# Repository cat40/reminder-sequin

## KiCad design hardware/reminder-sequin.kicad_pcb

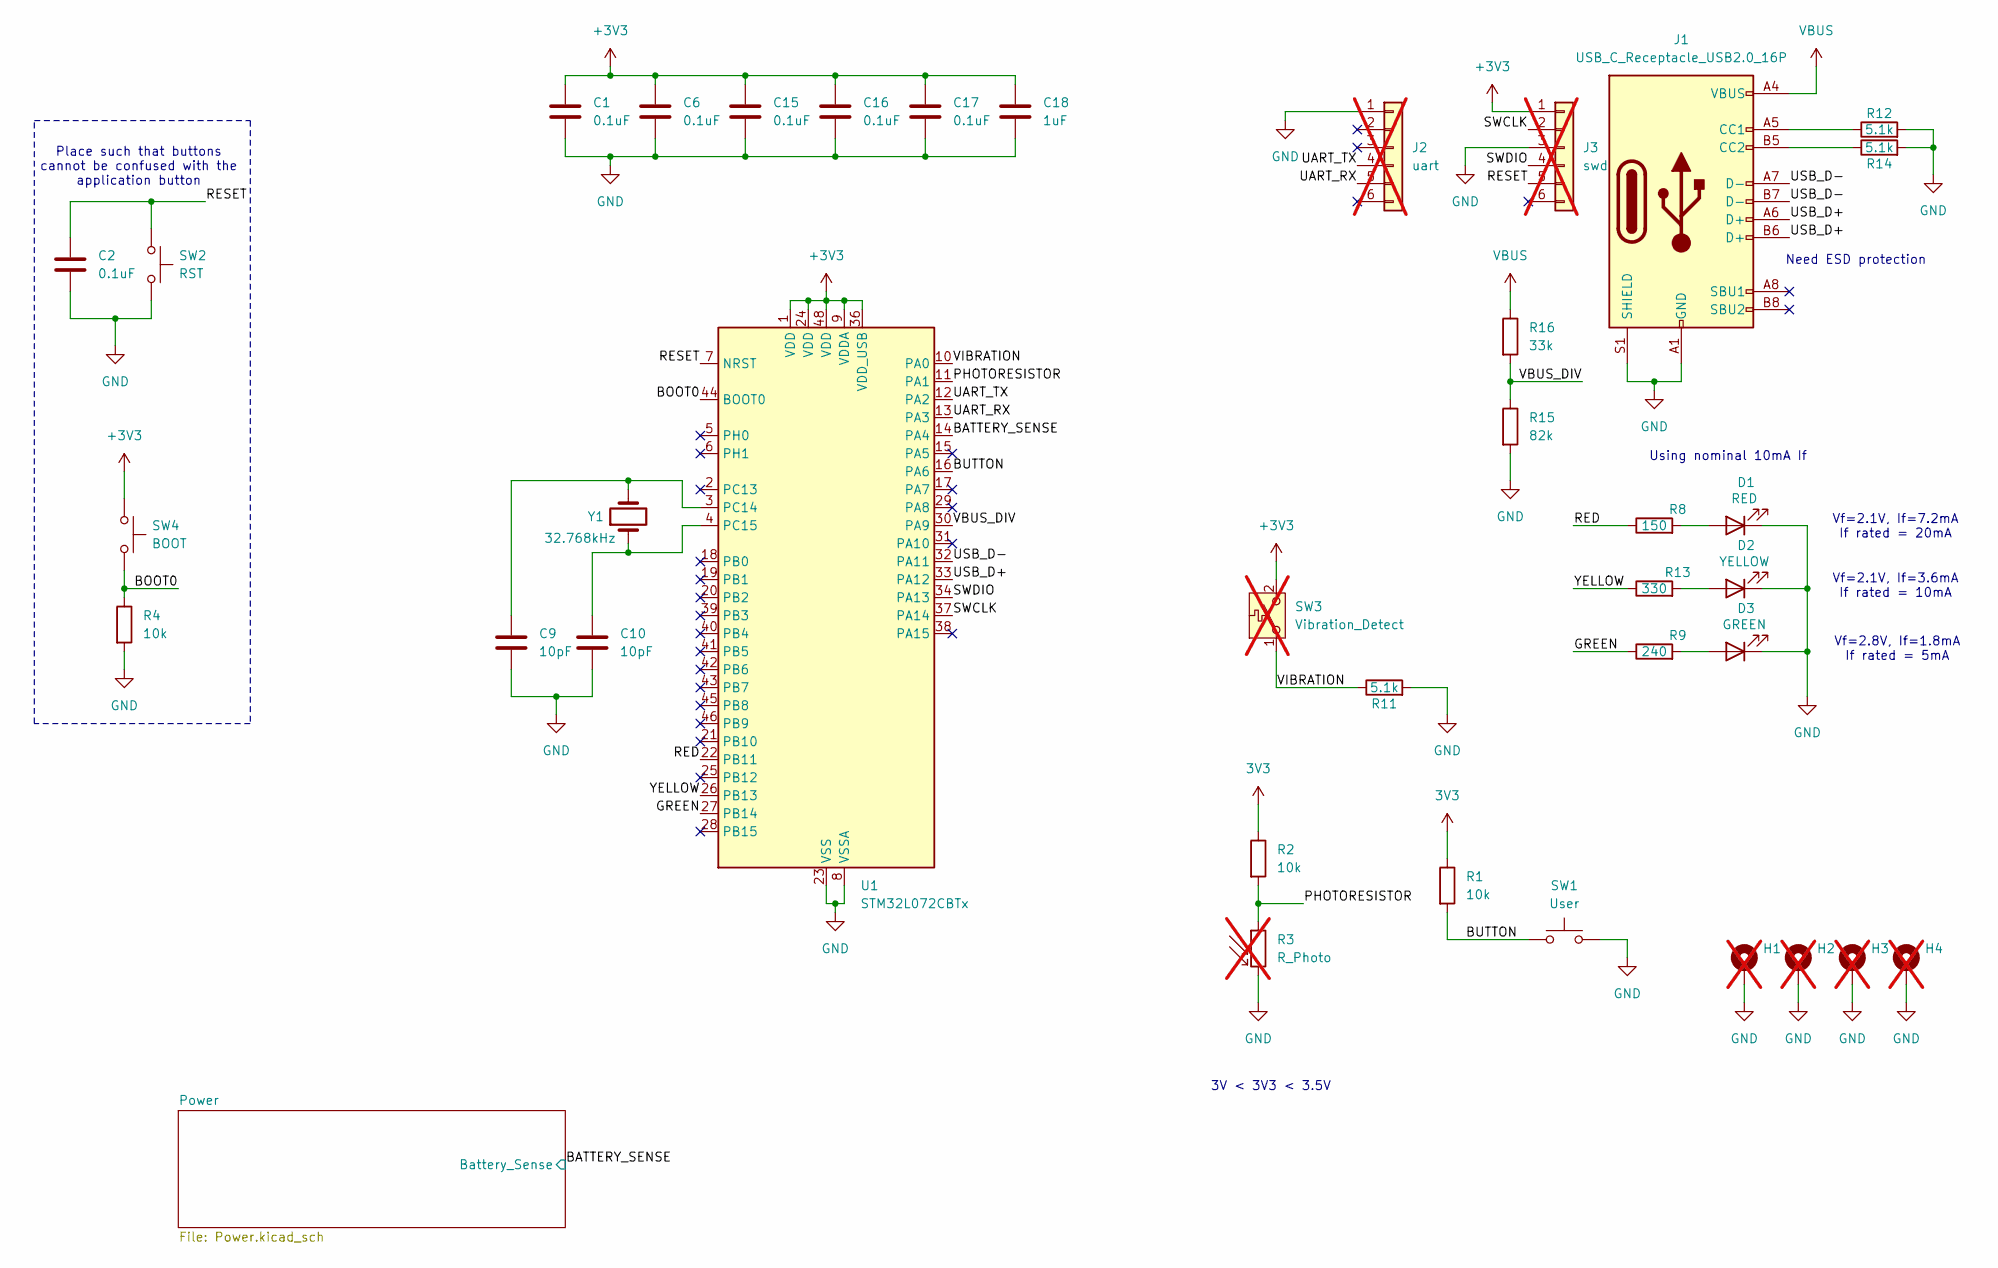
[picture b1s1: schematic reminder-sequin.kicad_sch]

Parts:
C1, C2, C6, C15, C16, C17: 0.1uF; C_0402_1005Metric; LCSC Part # C1525
C9, C10: 10pF; C_0402_1005Metric; LCSC Part # C32949
C18: 1uF; C_0805_2012Metric; LCSC Part # C28323
D1: RED; LED_0603_1608Metric; LCSC Part # C2286
D2: YELLOW; LED_0805_2012Metric; LCSC Part # C2296
D3: GREEN; LED_0805_2012Metric; LCSC Part # C2297
H1, H2, H3, H4: MountingHole_Pad; MountingHole_2.2mm_M2_ISO7380_Pad; not fitted
J1: USB_C_Receptacle_USB2.0_16P; USB_C_Receptacle_G-Switch_GT-USB-7010ASV; LCSC Part # C2988369
J2: uart; PinHeader_1x06_P2.54mm_Vertical; not fitted
J3: swd; PinHeader_1x06_P2.54mm_Vertical; not fitted
R1, R2, R4: 10k; R_0402_1005Metric; LCSC Part # C25744
R3: R_Photo; LED_D5.0mm_FlatTop; not fitted
R8: 150; R_0402_1005Metric; LCSC Part # C25082
R9: 240; R_0603_1608Metric; LCSC Part # C23350
R11, R12, R14: 5.1k; R_0402_1005Metric; LCSC Part # C25905
R13: 330; R_0603_1608Metric; LCSC Part # C23138
R15: 82k; R_0603_1608Metric; LCSC Part # C23254
R16: 33k; R_0402_1005Metric; LCSC Part # C25779
SW1: User; TS-1088-AR02016; LCSC Part # C720477
SW2: RST; TS-1088-AR02016; LCSC Part # C720477
SW3: Vibration_Detect; CP_Radial_D5.0mm_P2.00mm; not fitted
SW4: BOOT; TS-1088-AR02016; LCSC Part # C720477
U1: STM32L072CBTx; LQFP-48_7x7mm_P0.5mm
Y1: 32.768kHz; Crystal_SMD_3215-2Pin_3.2x1.5mm; LCSC Part # C32346

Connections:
3V3: R1.1, R2.1
+3V3: C1.2, C6.2, C15.2, C16.2, C17.2, C18.2, J3.1, SW3.2 (B), SW4.1, U1.1 (VDD), U1.9 (VDDA), U1.24 (VDD), U1.36 (VDD_USB), U1.48 (VDD); also elsewhere on the board
/BATTERY_SENSE: U1.14 (PA4); also elsewhere on the board
/BOOT0: R4.1, SW4.2, U1.44 (BOOT0)
/BUTTON: R1.2, SW1.1, U1.16 (PA6)
/GREEN: R9.1, U1.27 (PB14)
/PHOTORESISTOR: R2.2, R3.1, U1.11 (PA1)
/RED: R8.1, U1.22 (PB11)
/RESET: C2.1, J3.5, SW2.1, U1.7 (NRST)
/SWCLK: J3.2, U1.37 (PA14)
/SWDIO: J3.4, U1.34 (PA13)
/UART_RX: J2.5, U1.13 (PA3)
/UART_TX: J2.4, U1.12 (PA2)
/USB_D+: J1.A6 (D+), J1.B6 (D+), U1.33 (PA12)
/USB_D-: J1.A7 (D-), J1.B7 (D-), U1.32 (PA11)
/VBUS_DIV: R15.1, R16.2, U1.30 (PA9)
/VIBRATION: R11.1, SW3.1 (A), U1.10 (PA0)
/YELLOW: R13.1, U1.26 (PB13)
GND: C1.1, C2.2, C6.1, C9.2, C10.2, C15.1, C16.1, C17.1, C18.1, D1.1 (K), D2.1 (K), D3.1 (K), H1.1, H2.1, H3.1, H4.1, J1.A1 (GND), J1.A12 (GND), J1.B1 (GND), J1.B12 (GND), J1.S1 (SHIELD), J2.1, J3.3, R3.2, R4.2, R11.2, R12.2, R14.2, R15.2, SW1.2, SW2.2, U1.8 (VSSA), U1.23 (VSS), U1.35 (VSS), U1.47 (VSS); also elsewhere on the board
unnamed: D1.2 (A), R8.2
unnamed: D2.2 (A), R13.2
unnamed: D3.2 (A), R9.2
unnamed: J1.A5 (CC1), R12.1
unnamed: J1.B5 (CC2), R14.1
unnamed: C9.1, U1.3 (PC14), Y1.2
unnamed: C10.1, U1.4 (PC15), Y1.1
VBUS: J1.A4 (VBUS), J1.A9 (VBUS), J1.B4 (VBUS), J1.B9 (VBUS), R16.1; also elsewhere on the board

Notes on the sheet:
Vf=2.1V, If=3.6mA If rated = 10mA
Using nominal 10mA If
Need ESD protection
Vf=2.8V, If=1.8mA If rated = 5mA
Place such that buttons cannot be confused with the application button
Vf=2.1V, If=7.2mA If rated = 20mA
3V < 3V3 < 3.5V

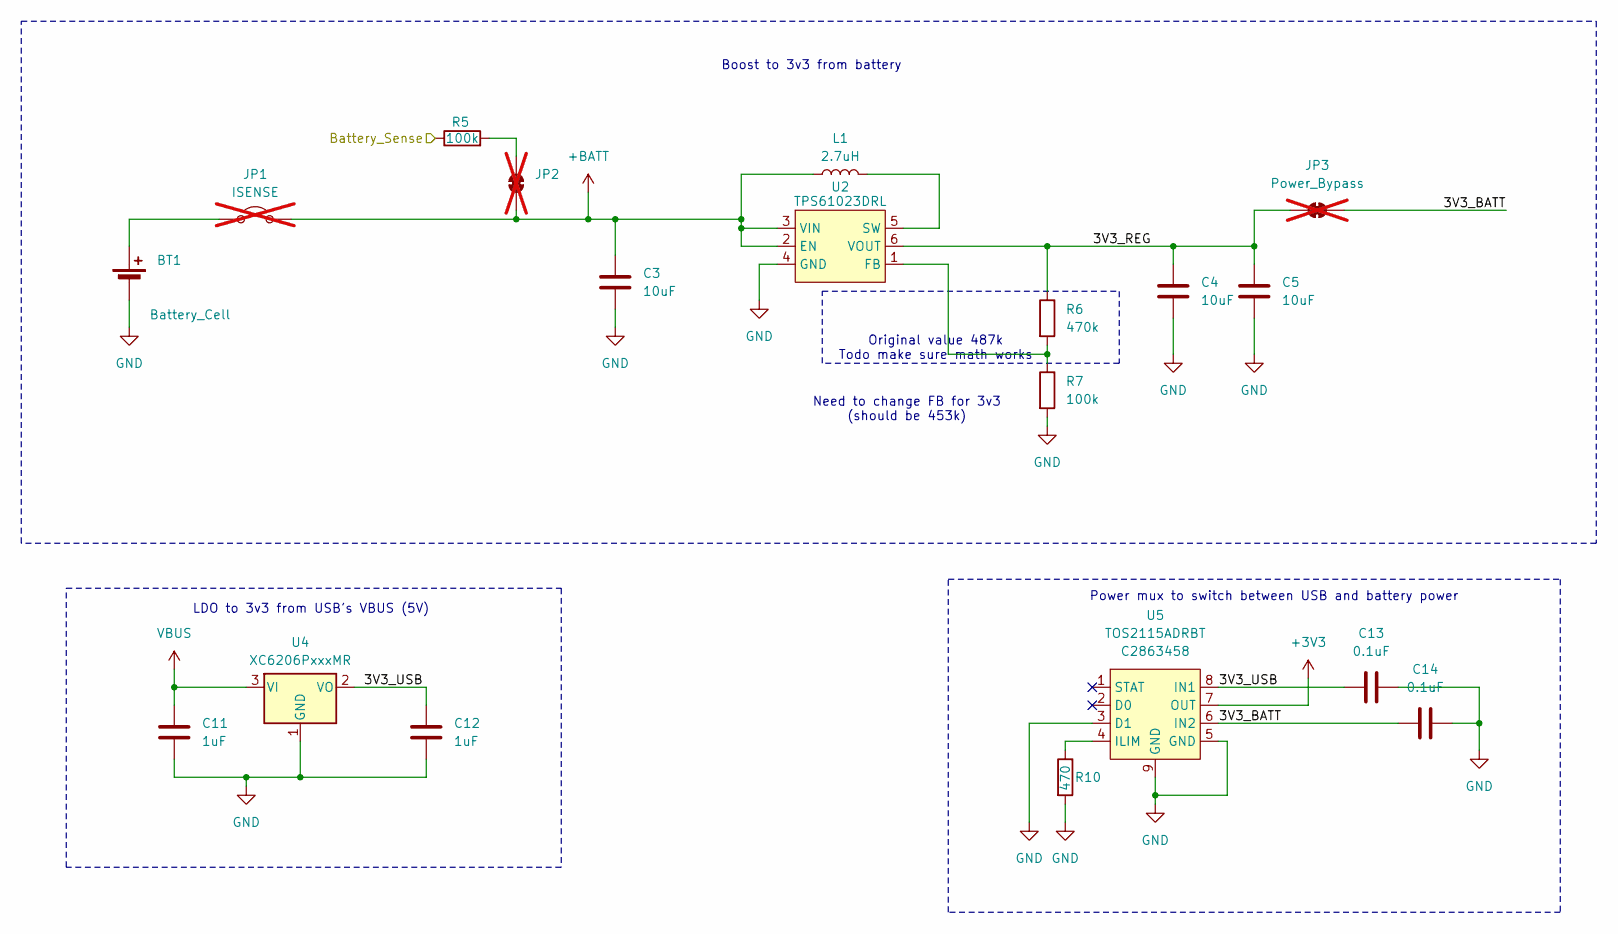
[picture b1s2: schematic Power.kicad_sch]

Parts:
BT1: Battery_Cell; BatteryHolder_Keystone_3002_1x2032; Digikey PN 36-3002-ND
C3, C4, C5: 10uF; C_0805_2012Metric; LCSC Part # C15850
C11, C12: 1uF; C_0805_2012Metric; LCSC Part # C28323
C13, C14: 0.1uF; C_0402_1005Metric; LCSC Part # C1525
JP1: ISENSE; SolderJumper-2_P1.3mm_Bridged2Bar_RoundedPad1.0x1.5mm; not fitted
JP2: SolderJumper_2_Bridged; SolderJumper-2_P1.3mm_Bridged2Bar_RoundedPad1.0x1.5mm; not fitted
JP3: Power_Bypass; SolderJumper-2_P1.3mm_Bridged2Bar_RoundedPad1.0x1.5mm; not fitted
L1: 2.7uH; Inductor_0806; LCSC Part # C139222
R5, R7: 100k; R_0402_1005Metric; LCSC Part # C25741
R6: 470k; R_0402_1005Metric; LCSC Part # C25790
R10: 470; R_0402_1005Metric; LCSC Part # C25117
U2: TPS61023DRL; SOT-563; LCSC Part # C919459
U4: XC6206PxxxMR; SOT-23-3; LCSC Part # C5446
U5: TOS2115ADRBT; VSON-8-1EP_3x3mm_P0.65mm_EP1.65x2.4mm; LCSC Part # C2863458

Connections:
+3V3: U5.7 (OUT); also elsewhere on the board
+BATT: C3.1, JP1.2 (B), JP2.1 (A), L1.1, U2.2 (EN), U2.3 (VIN)
/BATTERY_SENSE: R5.1; also elsewhere on the board
/Power/3V3_BATT: C14.2, JP3.2 (B), U5.6 (IN2)
/Power/3V3_REG: C4.1, C5.1, JP3.1 (A), R6.1, U2.6 (VOUT)
/Power/3V3_USB: C12.2, C13.2, U4.2 (VO), U5.8 (IN1)
GND: BT1.2 (-), C3.2, C4.2, C5.2, C11.1, C12.1, C13.1, C14.1, R7.2, R10.2, U2.4 (GND), U4.1 (GND), U5.3 (D1), U5.5 (GND), U5.9 (GND); also elsewhere on the board
unnamed: BT1.1 (+), JP1.1 (A)
unnamed: JP2.2 (B), R5.2
unnamed: R6.2, R7.1, U2.1 (FB)
unnamed: L1.2, U2.5 (SW)
unnamed: R10.1, U5.4 (ILIM)
VBUS: C11.2, U4.3 (VI); also elsewhere on the board

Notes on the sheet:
Boost to 3v3 from battery
Power mux to switch between USB and battery power
Original value 487k Todo make sure math works
LDO to 3v3 from USB's VBUS (5V)
Need to change FB for 3v3 (should be 453k)

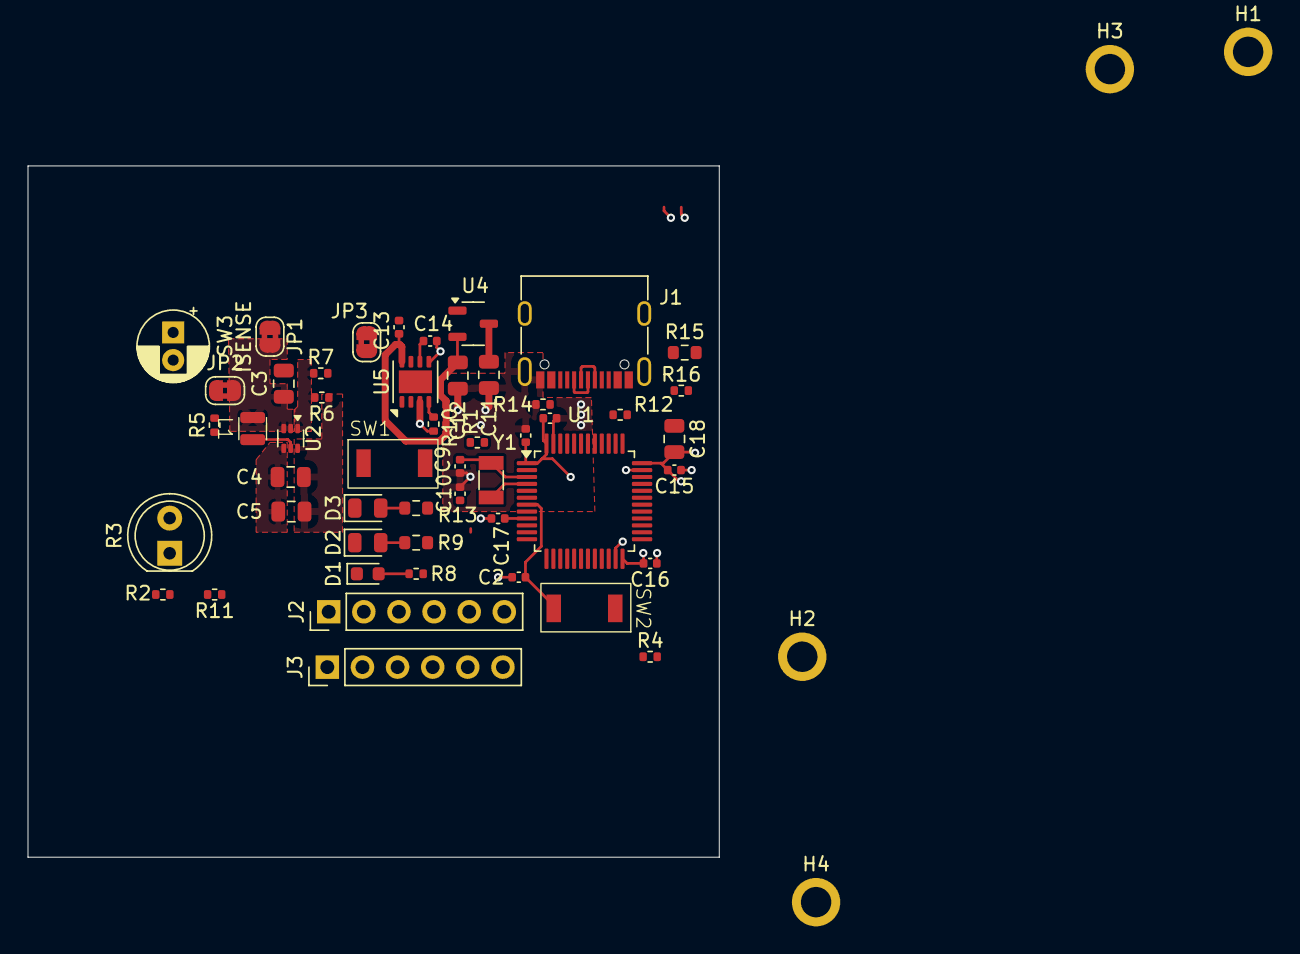
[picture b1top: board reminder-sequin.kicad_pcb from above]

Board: 4 copper layers, 50.0 x 50.0 mm, 55 parts (1 on the bottom side), 36 nets.

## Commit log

2025-06-29 initial electrical setup
2025-06-30 power system
2025-06-30 stuff
2025-07-01 switched to rp2040
2025-07-01 almost done
2025-07-02 more stuff
2025-07-02 assigned part numbers and footprints
2025-07-12 layout
2025-07-13 mounting holes
2025-08-22 redid design based on STM3201
2025-08-23 design polishing
2025-08-23 schematic is kinda finished now
2025-08-23 started layout
2025-08-23 BOM spreadsheet improvements
2025-08-25 bom improvements
2025-08-27 switched microcontrollers, again
2025-08-28 layout stuff
2025-08-29 more layout
